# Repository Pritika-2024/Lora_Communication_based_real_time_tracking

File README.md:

# LoRa GPS Tracking System

## Introduction
This project implements a long-range wireless tracking system using LoRa communication. An STM32-based transmitter acquires real-time GPS coordinates and transmits them over LoRa, while an ESP32-based receiver processes and displays the received data. The system is optimized for low-power, long-distance IoT tracking.

---

## Project Overview
The system consists of two nodes:
- **Transmitter (STM32 + GPS + LoRa)**  
- **Receiver (ESP32 + LoRa)**  

---

## Technical Details

### Baud Rate
- GPS: 9600 bps  
- Serial: 115200 bps  

### Frequency of Operation
- LoRa: **433 MHz**

### STM32 Programming and Debugging
- Programming via **ST-Link (SWD interface)**  
- Pins: SWCLK, SWDIO, GND, VCC  
- Supports debugging (breakpoints, step execution)

### Communication Interfaces
- LoRa → Uses SPI communication with STM32  
- GPS → Uses UART communication with STM32  

### Hardware Connections

**LoRa (SX1278 → STM32)**
- NSS (CS) → SPI Chip Select  
- SCK → SPI Clock  
- MOSI → SPI MOSI  
- MISO → SPI MISO  
- DIO0 → External interrupt pin  

**GPS (NEO-6M → STM32)**
- TX → STM32 RX  
- RX → STM32 TX  
- VCC → 3.3V  
- GND → GND  

**ST-Link (Programming)**
- SWDIO → STM32 SWDIO  
- SWCLK → STM32 SWCLK  
- GND → GND  
- 3.3V → VCC  

---

## PCB Design
The transmitter circuit integrates STM32 with GPS (UART) and LoRa (SPI). A custom PCB was designed in KiCad for compact integration.

## Schematic

---

## Components (BOM-Based)
- **STM32F103RBTx** (Main controller, LQFP-64)  
- **SX1278 LoRa Module (Ra-01)** (RF communication)  
- **NEO-6M GPS Module** (Location acquisition via UART)  
- **AP2112K-3.3 Voltage Regulator** (3.3V supply)  
- **Capacitors**  
  - 100nF (decoupling near ICs)  
  - 1µF (regulator stability)  
  - 10µF (bulk filtering)  
- **Resistors (10kΩ)** (pull-up/pull-down)  
- **Connectors**  
  - Battery input (2-pin)  
  - Reset header  
  - ST-Link header  

---

## Power Supply Design (External Power)
The system is powered using an external battery connected via a **2-pin header (BatteryConnector1)**.

- Regulated using **AP2112K-3.3 (LDO)**  
- 1µF capacitors at input/output for stability  
- 10µF bulk capacitor for transient response  
- 100nF capacitors for local decoupling  

### Power Flow
Battery → Regulator (3.3V) →  
STM32, LoRa, GPS  

Ensures stable 3.3V operation for all modules.

---

## PCB Layout

---

## Prototype
The hardware prototype validates real-time communication between transmitter and receiver.

---

## Basic Workflow
1. GPS provides latitude and longitude via UART  
2. STM32 processes and formats data  
3. LoRa transmits the data packet  
4. ESP32 receives and decodes the packet  
5. Output is displayed on serial monitor  

---

## Results

---

## Source Code

| File | Description |
|------|------------|
| [`src/transmitter.cpp`](./src/transmitter.cpp) | STM32 code for GPS data acquisition and LoRa transmission |
| [`src/receiver.cpp`](./src/receiver.cpp) | ESP32 code for LoRa reception and data decoding |

---

## Libraries Used

- **LoRa.h**  
  Used for interfacing with SX1278 module using SPI and handling packet transmission/reception.

- **TinyGPS++**  
  Parses raw NMEA data from GPS module into usable latitude and longitude values.

- **SPI.h**  
  Enables SPI communication between STM32/ESP32 and LoRa module.

- **SoftwareSerial (if used)**  
  Provides UART interface when hardware UART is limited (mainly for GPS).

---

## Tools Used
- KiCad (PCB design)  
- Arduino IDE (firmware development)  
- Embedded C (programming)

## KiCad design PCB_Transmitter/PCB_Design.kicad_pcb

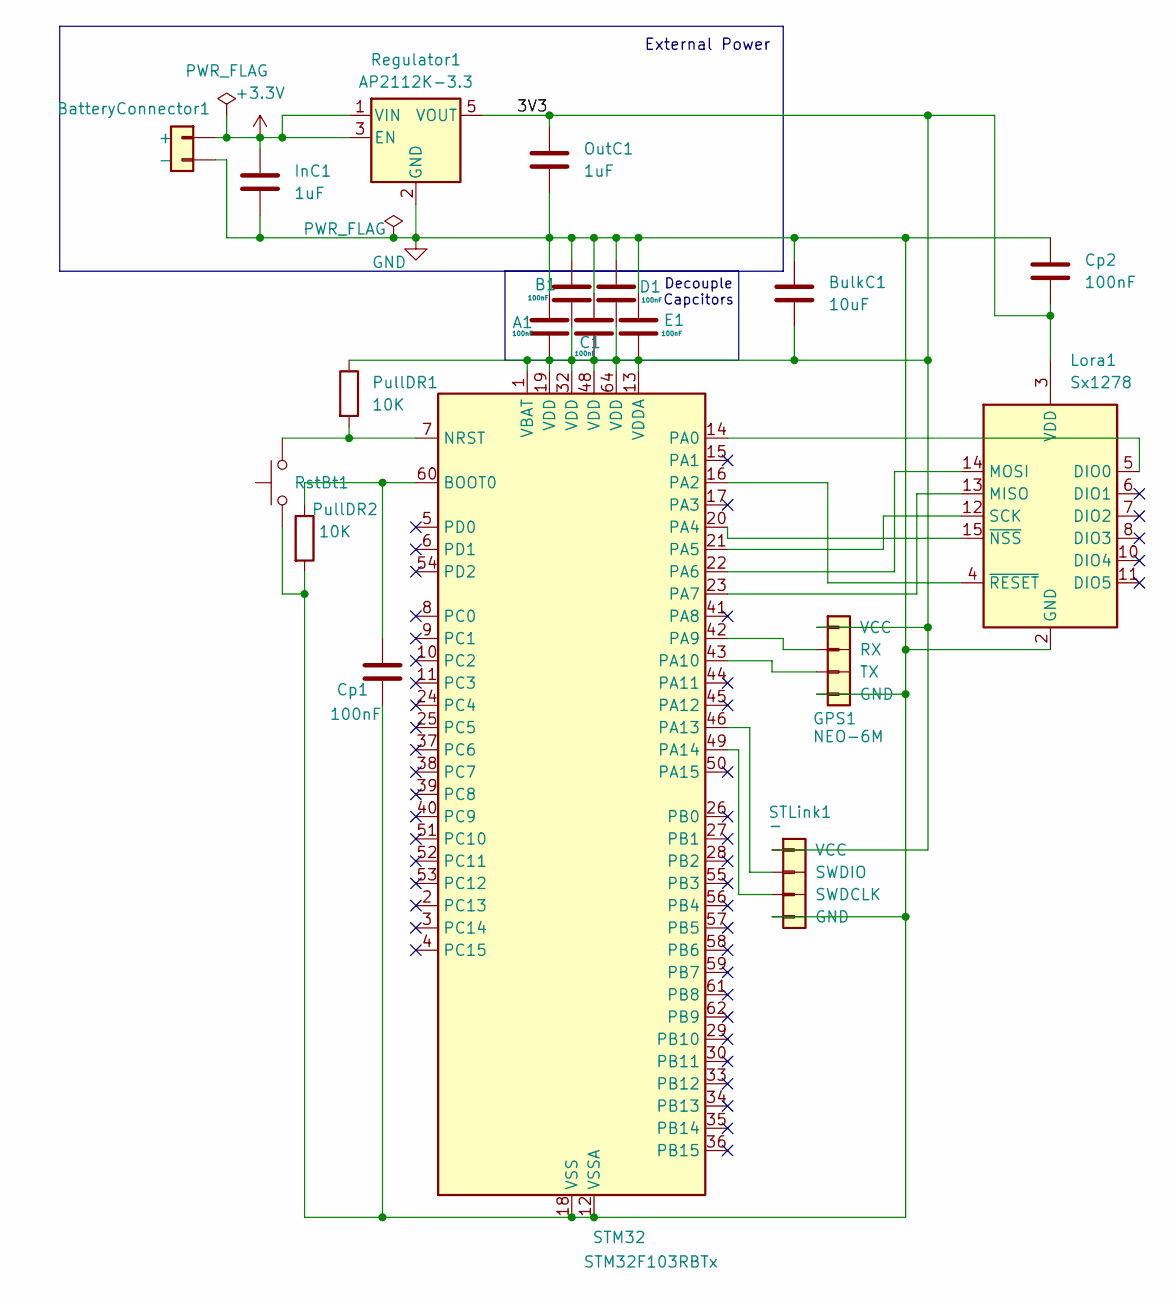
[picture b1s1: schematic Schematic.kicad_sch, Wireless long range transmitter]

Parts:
A1: 100nF; C_0603_1608Metric
B1: 100nF; C_0603_1608Metric
BatteryConnector1: PinHeader_1x02_P2.54mm_Vertical
BulkC1: 10uF; C_0805_2012Metric
C1: 100nF; C_0603_1608Metric
Cp1, Cp2: 100nF; C_0603_1608Metric
D1: 100nF; C_0603_1608Metric
E1: 100nF; C_0603_1608Metric
GPS1: NEO-6M; PinHeader_1x04_P2.54mm_Vertical
InC1: 1uF; C_0603_1608Metric
Lora1: Sx1278; Ai-Thinker-Ra-01-LoRa
OutC1: 1uF; C_0603_1608Metric
PullDR1, PullDR2: 10K; R_0603_1608Metric
Regulator1: AP2112K-3.3; SOT-23-5
RstBt1: PinHeader_1x02_P2.54mm_Vertical
STLink1: -; PinHeader_1x04_P2.54mm_Vertical
STM32: STM32F103RBTx; LQFP-64_10x10mm_P0.5mm

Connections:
+3.3V: BatteryConnector1.1 (+), InC1.1, Regulator1.1 (VIN), Regulator1.3 (EN)
/3V3: A1.2, B1.2, BulkC1.2, C1.2, Cp2.2, D1.2, E1.2, GPS1.1 (VCC), Lora1.3 (VDD), OutC1.1, PullDR1.1, Regulator1.5 (VOUT), STLink1.1 (VCC), STM32.1 (VBAT), STM32.13 (VDDA), STM32.19 (VDD), STM32.32 (VDD), STM32.48 (VDD), STM32.64 (VDD)
GND: A1.1, B1.1, BatteryConnector1.2 (-), BulkC1.1, C1.1, Cp1.2, Cp2.1, D1.1, E1.1, GPS1.4 (GND), InC1.2, Lora1.1 (GND), Lora1.2 (GND), Lora1.9 (GND), Lora1.16 (GND), OutC1.2, PullDR2.2, Regulator1.2 (GND), RstBt1.1, STLink1.4 (GND), STM32.12 (VSSA), STM32.18 (VSS), STM32.31 (VSS), STM32.47 (VSS), STM32.63 (VSS)
unnamed: GPS1.2 (RX), STM32.42 (PA9)
unnamed: GPS1.3 (TX), STM32.43 (PA10)
unnamed: Lora1.5 (DIO0), STM32.14 (PA0)
unnamed: Lora1.13 (MISO), STM32.23 (PA7)
unnamed: Lora1.14 (MOSI), STM32.22 (PA6)
unnamed: Lora1.12 (SCK), STM32.21 (PA5)
unnamed: Lora1.15 (~NSS), STM32.20 (PA4)
unnamed: Lora1.4 (~RESET), STM32.16 (PA2)
unnamed: STLink1.3 (SWDCLK), STM32.49 (PA14)
unnamed: STLink1.2 (SWDIO), STM32.46 (PA13)
unnamed: Cp1.1, PullDR2.1, STM32.60 (BOOT0)
unnamed: PullDR1.2, RstBt1.2, STM32.7 (NRST)

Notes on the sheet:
External Power
Decouple Capcitors

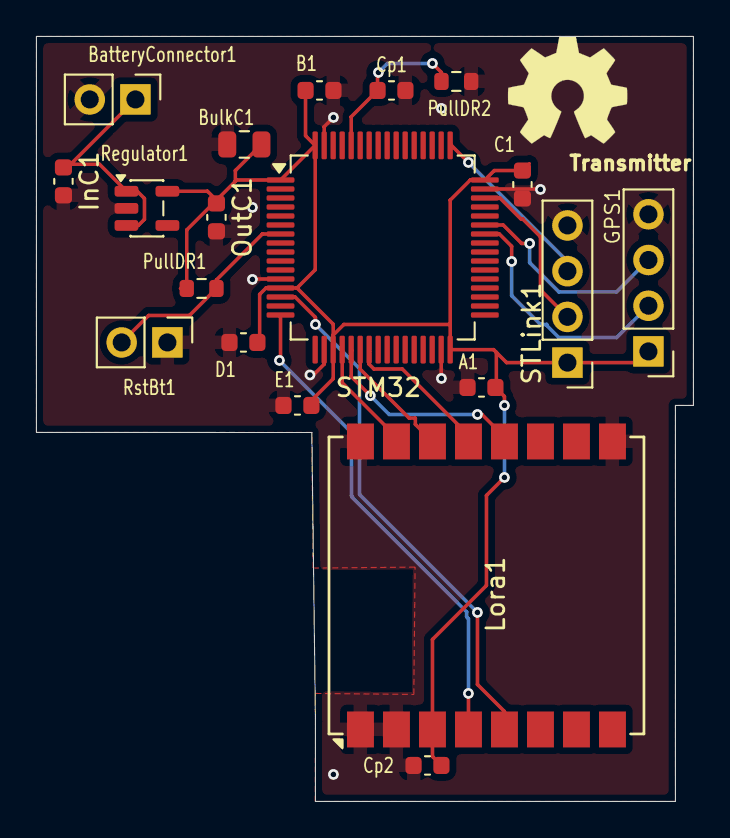
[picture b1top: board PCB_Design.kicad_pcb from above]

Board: 2 copper layers, 36.5 x 42.5 mm, 19 parts (0 on the bottom side), 15 nets.

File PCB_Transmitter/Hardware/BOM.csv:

Reference,Qty,Value,Footprint
"A1,B1,C1,Cp1,Cp2,D1,E1",7,100nF,Capacitor_SMD:C_0603_1608Metric
"BatteryConnector1,RstBt1",2,,Connector_PinHeader_2.54mm:PinHeader_1x02_P2.54mm_Vertical
BulkC1,1,10uF,Capacitor_SMD:C_0805_2012Metric
GPS1,1,NEO-6M,Connector_PinHeader_2.54mm:PinHeader_1x04_P2.54mm_Vertical
"InC1,OutC1",2,1uF,Capacitor_SMD:C_0603_1608Metric
Lora1,1,Sx1278,RF_Module:Ai-Thinker-Ra-01-LoRa
"PullDR1,PullDR2",2,10K,Resistor_SMD:R_0603_1608Metric
Regulator1,1,AP2112K-3.3,Package_TO_SOT_SMD:SOT-23-5
STLink1,1,-,Connector_PinHeader_2.54mm:PinHeader_1x04_P2.54mm_Vertical
STM32,1,STM32F103RBTx,Package_QFP:LQFP-64_10x10mm_P0.5mm

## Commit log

2026-03-31 newFiles
2026-03-31 Implement GPS + LoRa transmitter with emergency button
    This code initializes a LoRa transmitter that reads GPS data and sends it over LoRa. It includes emergency button functionality to send an emergency message.
2026-03-31 Add LoRa Receiver implementation in Receiver.cpp
2026-03-31 Revise README structure and add technical details
    Updated the README to reorganize sections and add technical details about the circuit and PCB design.
2026-03-31 Remove Circuit Implementation section from README
    Removed Circuit Implementation section and image from README.
